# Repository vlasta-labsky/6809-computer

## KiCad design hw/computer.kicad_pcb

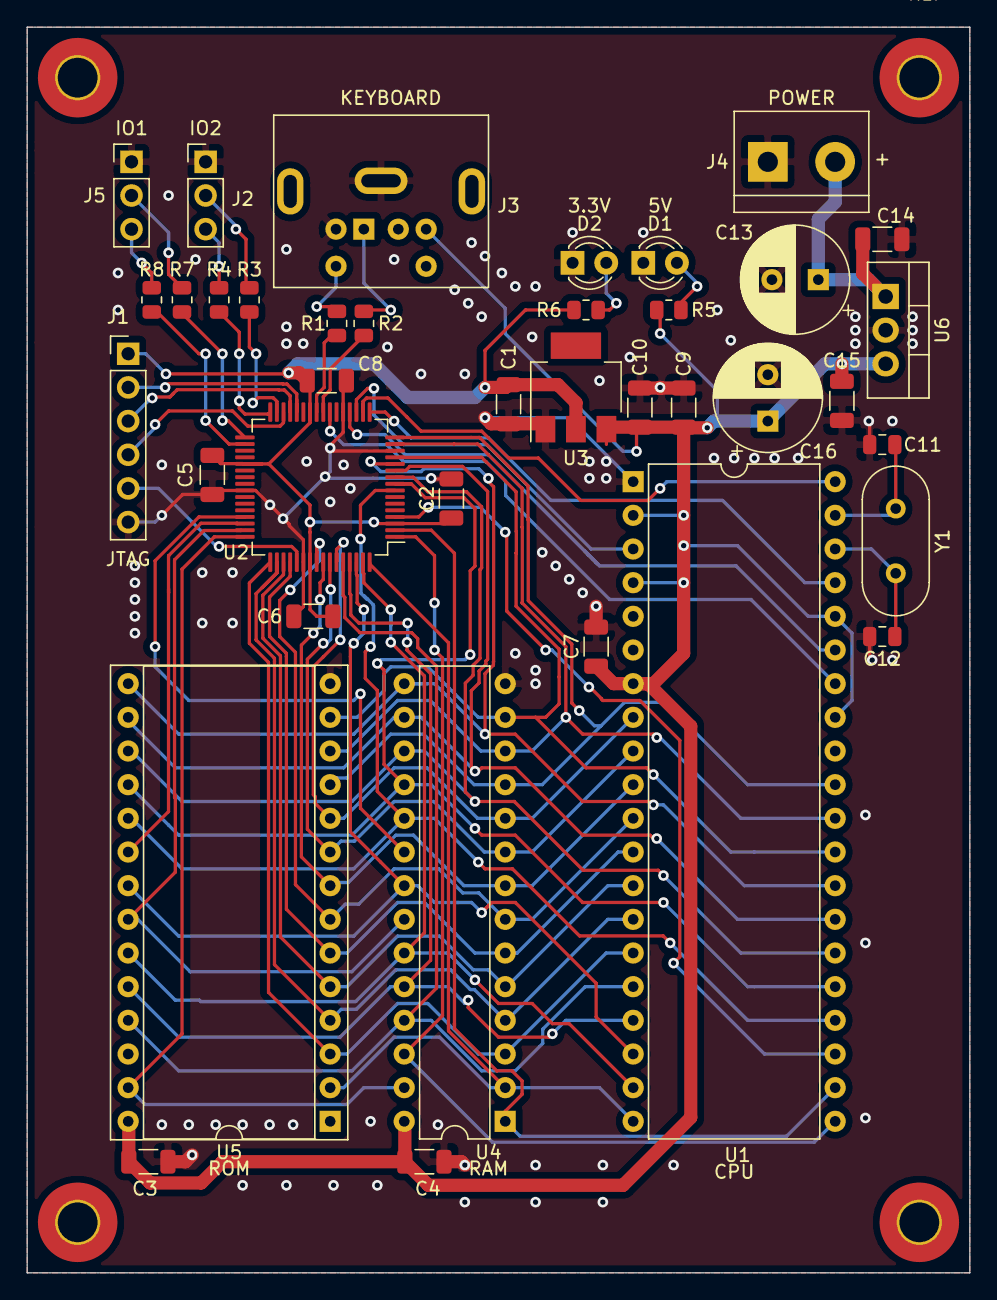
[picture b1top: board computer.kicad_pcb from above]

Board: 2 copper layers, 71.1 x 94.0 mm, 38 parts (0 on the bottom side), 58 nets.

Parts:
C1, C2, C3, C4, C5, C6, C7, C8, C9, C10, C14, C15: 100n; C_1206_3216Metric
C11, C12: 22p; C_0805_2012Metric
C13, C16: 1000u; CP_Radial_D8.0mm_P3.50mm
D1, D2: LED; LED_D3.0mm
J1: Conn_01x06_Male; PinHeader_1x06_P2.54mm_Vertical
J2, J5: Conn_01x03_Male; PinHeader_1x03_P2.54mm_Vertical
J3: Mini-DIN-6; Connector_Mini-DIN_Female_6Pin_2rows
J4: Screw_Terminal_01x02; TerminalBlock_bornier-2_P5.08mm
R1, R2, R3, R4, R7, R8: 100R; R_0805_2012Metric
R5, R6: 1k; R_0805_2012Metric
U1: MC6809; DIP-40_W15.24mm
U2: XC9572XL-VQ64; TQFP-64_10x10mm_P0.5mm
U3: NCP1117-3.3_SOT223; SOT-223-3_TabPin2
U4: UM61256; DIP-28_W7.62mm
U5: 28C256; DIP-28_W15.24mm_Socket
U6: LM7805_TO220; TO-220-3_Vertical
Y1: Crystal; Crystal_HC49-U_Vertical

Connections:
+3V3: C1.1, C2.1, C5.1, C6.1, C8.1, J1.1, R6.1, U2.3, U2.26, U2.37, U2.55, U3.2
+5V: C3.1, C4.1, C7.1, C9.1, C10.1, C15.1, C16.1, J3.4, R5.1, U1.2, U1.4, U1.7, U1.33, U1.36, U3.3, U4.28, U5.28, U6.3
/A0: U1.8, U2.59, U4.10, U5.10
/A1: U1.9, U2.58, U4.9, U5.9
/A2: U1.10, U2.57, U4.8, U5.8
/A3: U1.11, U2.56, U4.7, U5.7
/A4: U1.12, U2.52, U4.6, U5.6
/A5: U1.13, U2.51, U4.5, U5.5
/A6: U1.14, U2.50, U4.4, U5.4
/A7: U1.15, U2.49, U4.3, U5.3
/A8: U1.16, U2.60, U4.25, U5.25
/A9: U1.17, U2.61, U4.24, U5.24
/A10: U1.18, U2.62, U4.21, U5.21
/A11: U1.19, U2.63, U4.23, U5.23
/A12: U1.20, U2.64, U4.2, U5.2
/A13: U1.21, U2.1, U4.26
/A14: U1.22, U2.2, U4.1
/A15: U1.23, U2.4
/D0: U1.31, U2.16, U4.11, U5.11
/D1: U1.30, U2.15, U4.12, U5.12
/D2: U1.29, U2.13, U4.13, U5.13
/D3: U1.28, U2.12, U4.15, U5.15
/D4: U1.27, U2.11, U4.16, U5.16
/D5: U1.26, U2.10, U4.17, U5.17
/D6: U1.25, U2.9, U4.18, U5.18
/D7: U1.24, U2.8, U4.19, U5.19
E: U1.34, U2.23
GND: C1.2, C2.2, C3.2, C4.2, C5.2, C6.2, C7.2, C8.2, C9.2, C10.2, C11.2, C12.2, C13.2, C14.2, C15.2, C16.2, D1.1, D2.1, J1.6, J2.1, J3.3, J4.1, J5.1, U1.1, U2.14, U2.21, U2.41, U2.54, U3.1, U4.14, U5.14, U6.2
HALT: U1.40, U2.18
IRQ: U1.3, U2.19
unnamed: C11.1, U1.39, Y1.1
unnamed: C12.1, U1.38, Y1.2
unnamed: C13.1, C14.1, J4.2, U6.1
unnamed: D1.2, R5.2
unnamed: D2.2, R6.2
unnamed: J1.2, U2.28
unnamed: J1.3, U2.29
unnamed: J1.4, U2.30
unnamed: J1.5, U2.53
unnamed: J2.2, R3.1
unnamed: J2.3, R4.1
unnamed: J3.1, R2.1
unnamed: J3.5, R1.1
unnamed: J5.2, R7.1
unnamed: J5.3, R8.1
unnamed: R1.2, U2.25
unnamed: R2.2, U2.24
unnamed: R3.2, U2.31
unnamed: R4.2, U2.32
unnamed: R7.2, U2.33
unnamed: R8.2, U2.34
Q: U1.35, U2.20
R: U2.47, U4.22, U5.22
RAM: U2.45, U4.20
RESET: U1.37, U2.17
ROM: U2.46, U5.20
RW: U1.32, U2.44
W: U2.48, U4.27, U5.27

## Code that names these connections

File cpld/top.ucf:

#PACE: Start of Constraints generated by PACE

#PACE: Start of PACE I/O Pin Assignments
NET "ADDR<0>"  LOC = "P59"  ; 
NET "ADDR<10>"  LOC = "P62"  ; 
NET "ADDR<11>"  LOC = "P63"  ; 
NET "ADDR<12>"  LOC = "P64"  ; 
NET "ADDR<13>"  LOC = "P1"  ; 
NET "ADDR<14>"  LOC = "P2"  ; 
NET "ADDR<15>"  LOC = "P4"  ; 
NET "ADDR<1>"  LOC = "P58"  ; 
NET "ADDR<2>"  LOC = "P57"  ; 
NET "ADDR<3>"  LOC = "P56"  ; 
NET "ADDR<4>"  LOC = "P52"  ; 
NET "ADDR<5>"  LOC = "P51"  ; 
NET "ADDR<6>"  LOC = "P50"  ; 
NET "ADDR<7>"  LOC = "P49"  ; 
NET "ADDR<8>"  LOC = "P60"  ; 
NET "ADDR<9>"  LOC = "P61"  ; 
NET "DATA<0>"  LOC = "P16"  ; 
NET "DATA<1>"  LOC = "P15"  ; 
NET "DATA<2>"  LOC = "P13"  ; 
NET "DATA<3>"  LOC = "P12"  ; 
NET "DATA<4>"  LOC = "P11"  ; 
NET "DATA<5>"  LOC = "P10"  ; 
NET "DATA<6>"  LOC = "P9"  ; 
NET "DATA<7>"  LOC = "P8"  ; 
NET "E"  LOC = "P23"  ; 
NET "HALT"  LOC = "P18"  ; 
NET "IRQ"  LOC = "P19"  ; 
NET "KEYBOARD_CLK"  LOC = "P25"  ;
NET "KEYBOARD_DATA"  LOC = "P24"  ;
NET "Q"  LOC = "P20"  ; 
NET "R"  LOC = "P47"  ; 
NET "RAM"  LOC = "P45"  ; 
NET "RESET"  LOC = "P17"  ; 
NET "ROM"  LOC = "P46"  ; 
NET "RW"  LOC = "P44"  ; 
NET "TXD"  LOC = "P33"  ; 
NET "TXD2"  LOC = "P31"  ; 
NET "W"  LOC = "P48"  ; 

#PACE: Start of PACE Area Constraints

#PACE: Start of PACE Prohibit Constraints

#PACE: End of Constraints generated by PACE

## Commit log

2021-06-18 Add initial CPLD code and Kicad HW
2021-06-18 Add simple test SW
2021-06-20 Improve test program
2021-06-20 JTAG->CPLD->EEPROM programming tool
2021-06-20 Update CPLD code
2021-06-30 Add another test program
2024-05-13 Add more sw
2024-05-13 Add PS2 to CPLD
2024-05-13 Remove outdated xise file
